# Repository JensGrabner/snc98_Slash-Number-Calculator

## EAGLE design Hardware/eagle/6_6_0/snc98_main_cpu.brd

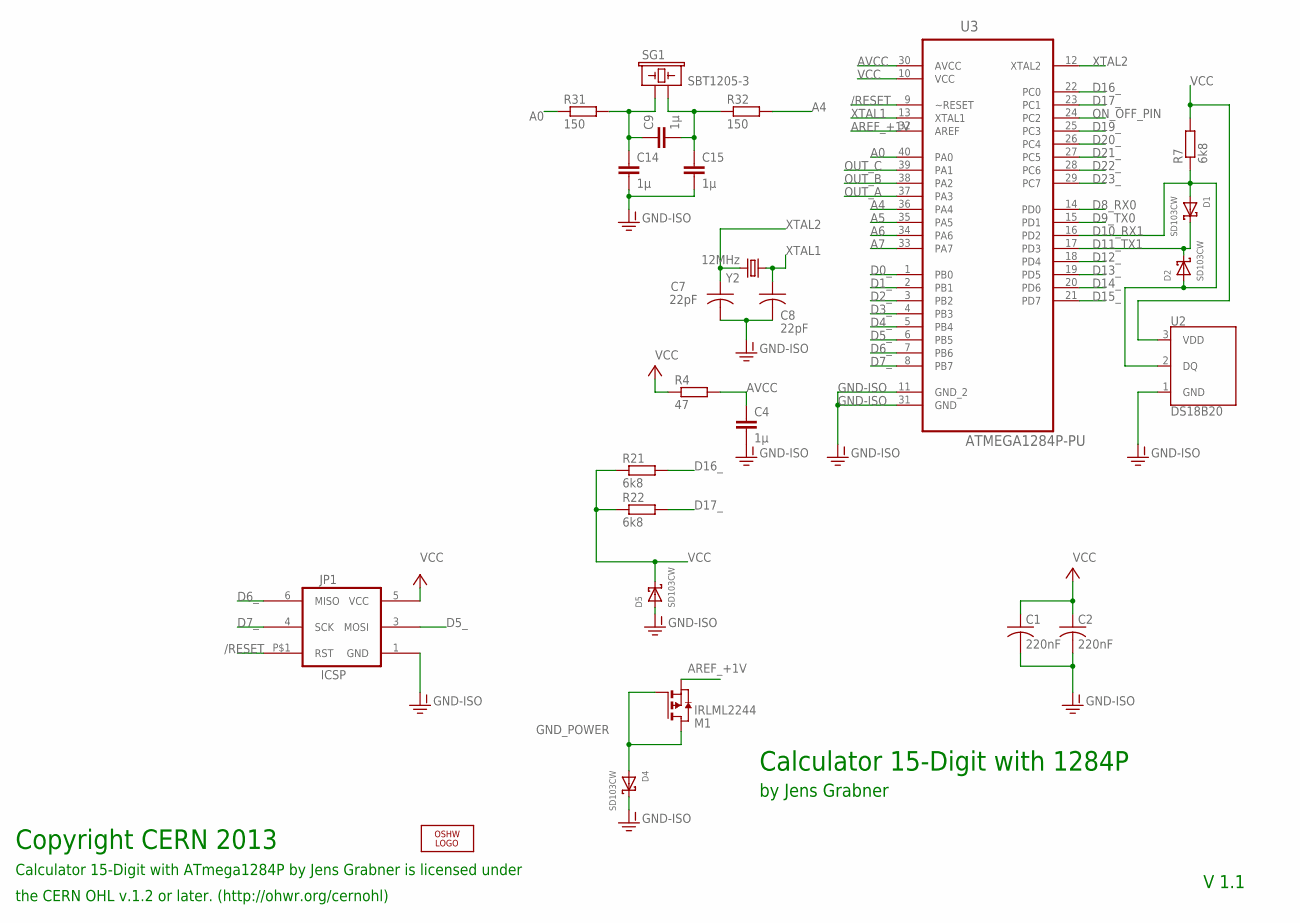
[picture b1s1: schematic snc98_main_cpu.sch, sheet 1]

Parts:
C1, C2: 220nF; C1206K
C4, C9, C14, C15: 1µ; C1206K
C7, C8: 22pF; C0805K
D1: SD103CW; SOD-323; MPN SD103CW-7-F
D2: SD103CW; SOD-123; MPN SD103CW-7-F
D4, D5: SD103CW; SOD-123F; MPN SD103CW-7-F
JP1: ICSP; 2X3_SMD_VERTICAL
LOGO1: OSHW_LOGO_8MILX0150-NT; OSHW_8X150_NOTEXT
M1: IRLML2244; SOT-23; MPN IRLML2244TRPBF
R4: 47; R1206
R7, R21, R22: 6k8; R1206
R31, R32: 150; R1206
SG1: SBT1205-3; BUZZER-12MM-NS
U2: DS18B20; TO-92-AMMO
U3: ATMEGA1284P-PU; DIP254P1524X483-40
Y2: 12MHz; HC49U-V

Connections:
/RESET: JP1.P$1 (RST), U3.9 (~RESET); also elsewhere on the board
A0: R31.1, U3.40 (PA0)
A4: R32.2, U3.36 (PA4)
A5: U3.35 (PA5); also elsewhere on the board
A6: U3.34 (PA6); also elsewhere on the board
A7: U3.33 (PA7); also elsewhere on the board
AREF_+1V: M1.2 (S), U3.32 (AREF); also elsewhere on the board
AVCC: C4.1, R4.2, U3.30 (AVCC)
D0_: U3.1 (PB0); also elsewhere on the board
D1_: U3.2 (PB1); also elsewhere on the board
D2_: U3.3 (PB2); also elsewhere on the board
D3_: U3.4 (PB3); also elsewhere on the board
D4_: U3.5 (PB4); also elsewhere on the board
D5_: JP1.3 (MOSI), U3.6 (PB5)
D6_: JP1.6 (MISO), U3.7 (PB6); also elsewhere on the board
D7_: JP1.4 (SCK), U3.8 (PB7); also elsewhere on the board
D8_RX0: U3.14 (PD0); also elsewhere on the board
D9_TX0: U3.15 (PD1); also elsewhere on the board
D10_RX1: D1.A, D2.A, R7.1, U2.2 (DQ), U3.16 (PD2)
D11_TX1: D1.C, D2.C, U3.17 (PD3)
D12_: U3.18 (PD4)
D13_: U3.19 (PD5); also elsewhere on the board
D14_: U3.20 (PD6); also elsewhere on the board
D15_: U3.21 (PD7); also elsewhere on the board
D16_: R21.2, U3.22 (PC0)
D17_: R22.2, U3.23 (PC1)
D19_: U3.25 (PC3); also elsewhere on the board
D20_: U3.26 (PC4); also elsewhere on the board
D21_: U3.27 (PC5); also elsewhere on the board
D22_: U3.28 (PC6); also elsewhere on the board
D23_: U3.29 (PC7); also elsewhere on the board
GND-ISO: C1.2, C2.2, C4.2, C7.2, C8.2, C14.2, C15.2, D4.C, D5.A, JP1.1 (GND), U2.1 (GND), U3.11 (GND_2), U3.31 (GND); also elsewhere on the board
GND_POWER: D4.A, M1.1 (G), M1.3 (D)
unnamed: C9.2, C15.1, R32.1, SG1.- (2)
unnamed: C9.1, C14.1, R31.2, SG1.+ (1)
ON_OFF_PIN: U3.24 (PC2); also elsewhere on the board
OUT_A: U3.37 (PA3); also elsewhere on the board
OUT_B: U3.38 (PA2); also elsewhere on the board
OUT_C: U3.39 (PA1); also elsewhere on the board
VCC: C1.1, C2.1, D5.C, JP1.5 (VCC), R4.1, R7.2, R21.1, R22.1, U2.3 (VDD), U3.10 (VCC); also elsewhere on the board
XTAL1: C8.1, U3.13 (XTAL1), Y2.1
XTAL2: C7.1, U3.12 (XTAL2), Y2.2

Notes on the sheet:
Calculator 15-Digit with 1284P
by Jens Grabner
V 1.1
Calculator 15-Digit with ATmega1284P by Jens Grabner is licensed under
Copyright CERN 2013
the CERN OHL v.1.2 or later. (http://ohwr.org/cernohl)

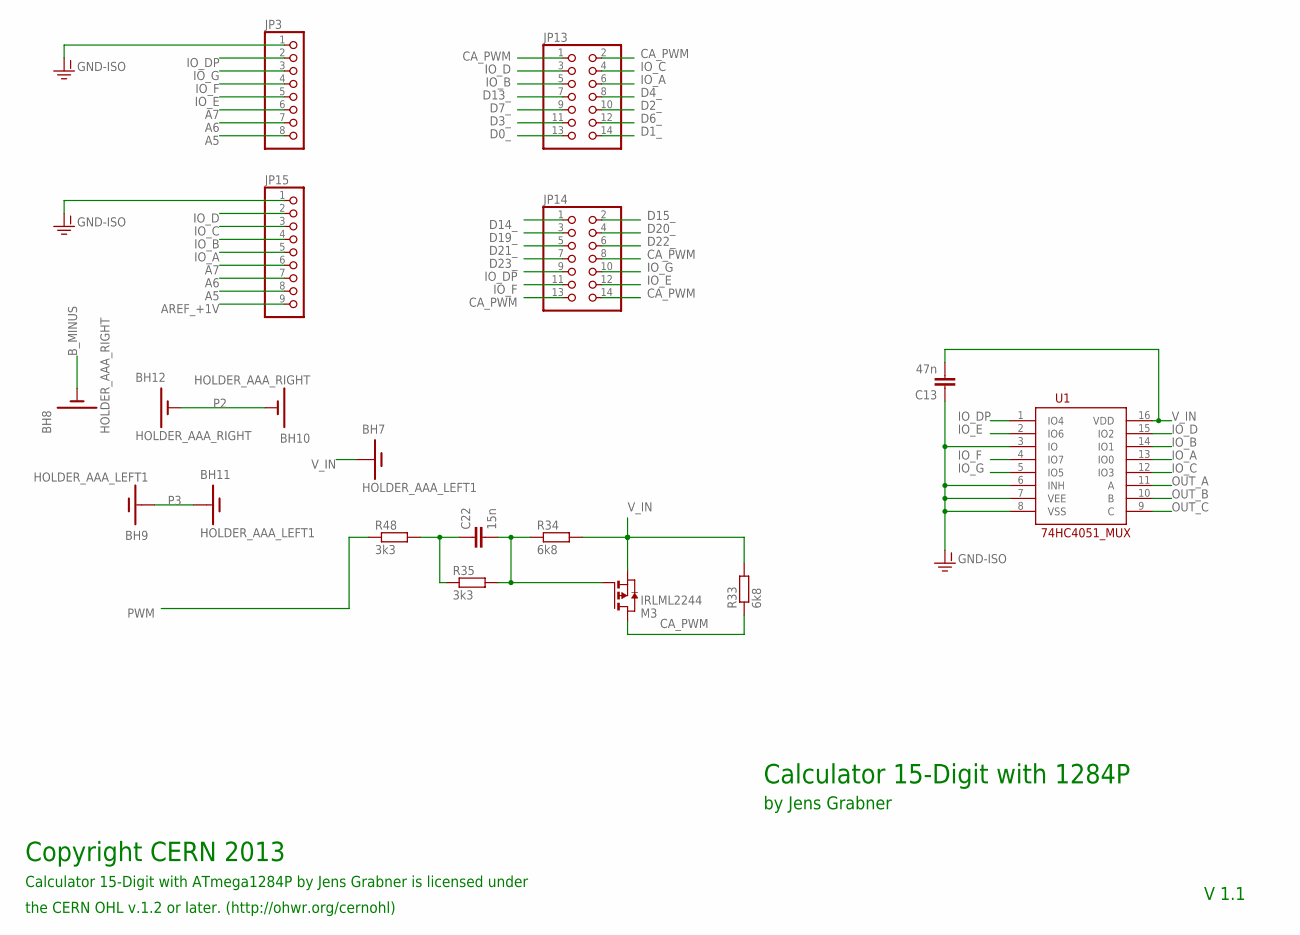
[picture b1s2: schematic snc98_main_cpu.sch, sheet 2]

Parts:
BH7, BH9, BH11: HOLDER_AAA_LEFT1; BATTERY-AAA-LEFT
BH8, BH10, BH12: HOLDER_AAA_RIGHT; BATTERY-AAA-RIGHT
C13: 47n; C1206K
C22: 15n; C1206K
JP3: PINHD-1X8CLEANBIG; 1X08-CLEANBIG
JP13, JP14: PINHD-2X7; 2X07
JP15: PINHD-1X9; 1X09-BIG
M3: IRLML2244; SOT-23; MPN IRLML2244TRPBF
R33, R34: 6k8; R1206
R35, R48: 3k3; R1206
U1: 74HC4051_MUX; SO16

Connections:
A5: JP3.8, JP15.8; also elsewhere on the board
A6: JP3.7, JP15.7; also elsewhere on the board
A7: JP3.6, JP15.6; also elsewhere on the board
A8: C22.1, R35.1, R48.2
AREF_+1V: JP15.9; also elsewhere on the board
B_MINUS: BH8.M1, BH8.M2, BH8.M3, BH8.M4; also elsewhere on the board
CA_PWM: JP13.1, JP13.2, JP14.8, JP14.13, JP14.14, M3.3 (D), R33.1
D0_: JP13.13; also elsewhere on the board
D1_: JP13.14; also elsewhere on the board
D2_: JP13.10; also elsewhere on the board
D3_: JP13.11; also elsewhere on the board
D4_: JP13.8; also elsewhere on the board
D6_: JP13.12; also elsewhere on the board
D7_: JP13.9; also elsewhere on the board
D13_: JP13.7; also elsewhere on the board
D14_: JP14.1; also elsewhere on the board
D15_: JP14.2; also elsewhere on the board
D19_: JP14.3; also elsewhere on the board
D20_: JP14.4; also elsewhere on the board
D21_: JP14.5; also elsewhere on the board
D22_: JP14.6; also elsewhere on the board
D23_: JP14.7; also elsewhere on the board
GND-ISO: C13.1, JP3.1, JP15.1, U1.3 (IO), U1.6 (INH), U1.7 (VEE), U1.8 (VSS); also elsewhere on the board
IO_A: JP13.6, JP15.5, U1.13 (IO0)
IO_B: JP13.5, JP15.4, U1.14 (IO1)
IO_C: JP13.4, JP15.3, U1.12 (IO3)
IO_D: JP13.3, JP15.2, U1.15 (IO2)
IO_DP: JP3.2, JP14.9, U1.1 (IO4)
IO_E: JP3.5, JP14.12, U1.2 (IO6)
IO_F: JP3.4, JP14.11, U1.4 (IO7)
IO_G: JP3.3, JP14.10, U1.5 (IO5)
unnamed: C22.2, M3.1 (G), R34.1, R35.2
OUT_A: U1.11 (A); also elsewhere on the board
OUT_B: U1.10 (B); also elsewhere on the board
OUT_C: U1.9 (C); also elsewhere on the board
P2: BH10.M1, BH10.M2, BH10.M3, BH10.M4, BH12.M1, BH12.M2, BH12.M3, BH12.M4
P3: BH9.P1, BH9.P2, BH9.P3, BH9.P4, BH11.P1, BH11.P2, BH11.P3, BH11.P4
PWM: R48.1
V_IN: BH7.P1, BH7.P2, BH7.P3, BH7.P4, C13.2, M3.2 (S), R33.2, R34.2, U1.16 (VDD); also elsewhere on the board

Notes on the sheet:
Calculator 15-Digit with 1284P
by Jens Grabner
V 1.1
Calculator 15-Digit with ATmega1284P by Jens Grabner is licensed under
Copyright CERN 2013
the CERN OHL v.1.2 or later. (http://ohwr.org/cernohl)

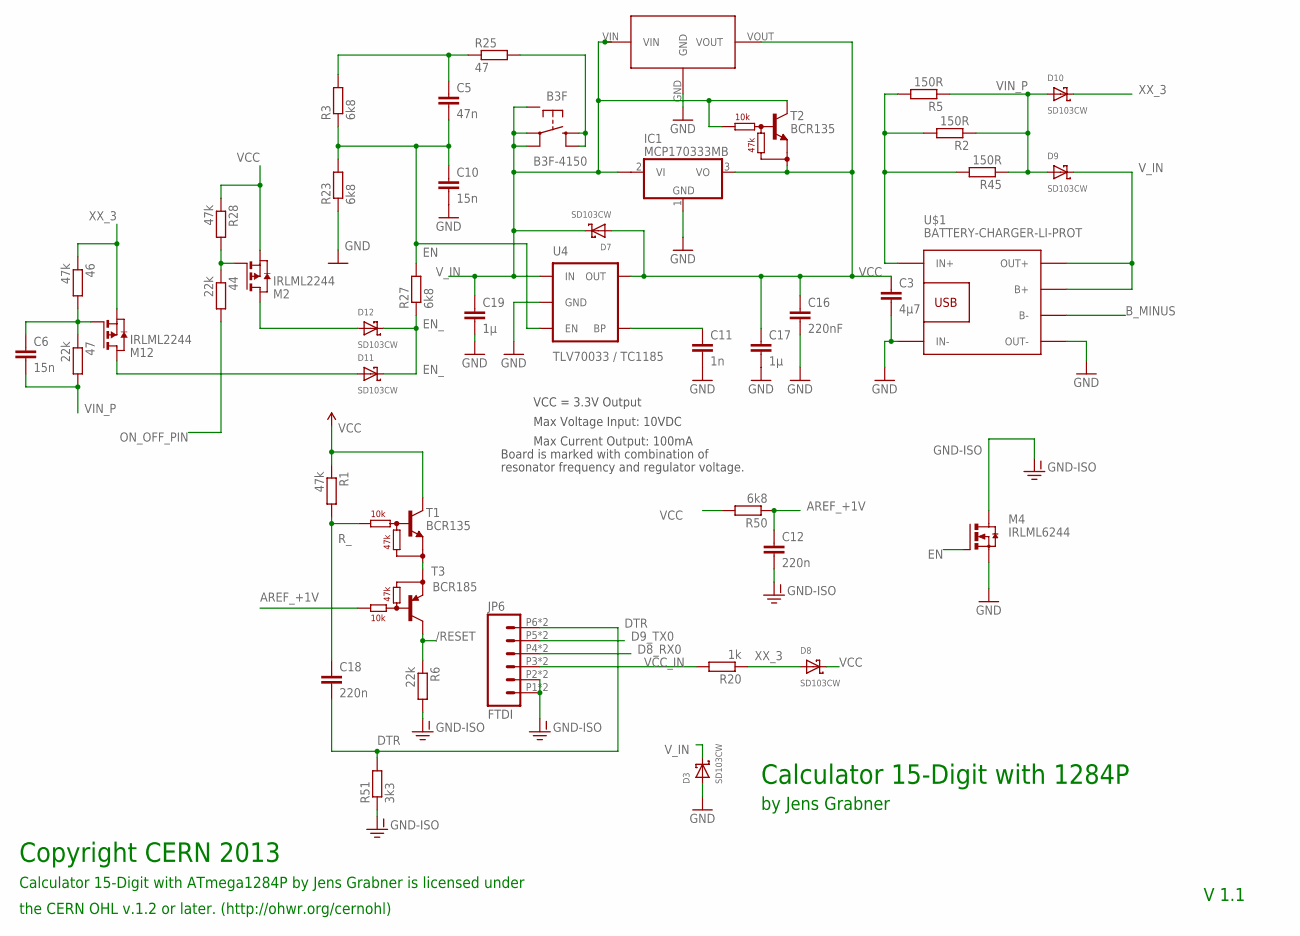
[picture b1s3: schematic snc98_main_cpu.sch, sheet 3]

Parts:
44, 47: 22k; R1206
46: 47k; R1206
C3: 4µ7; C1206K
C5: 47n; C1206K
C6, C10: 15n; C1206K
C11: 1n; 0805
C12: 220n; 0805
C16: 220nF; 0805
C17, C19: 1µ; C1206K
C18: 220n; C1206K
D3, D7, D8, D9, D10, D11, D12: SD103CW; SOD-123F; MPN SD103CW-7-F
IC1: MCP170333MB; SOT89
JP6: FTDI; 1X06_LOCK
M2, M12: IRLML2244; SOT-23; MPN IRLML2244TRPBF
M4: IRLML6244; SOT-23; MPN IRLML6244TRPBF
R1, R28: 47k; R1206
R2: 150R; 0204/5
R3, R23, R27, R50: 6k8; R1206
R5: 150R; 0207/10
R6: 22k; R1206
R20: 1k; R1206
R25: 47; R1206
R45: 150R; R1206
R51: 3k3; R1206
S3: B3F-4150; TACTILE-PTH-12MM; MPN B3F4150
T1, T2: BCR135; SOT23-BEC; MPN BCR135E6327HTSA1
T3: BCR185; SOT23-R_INFINEON; MPN DTA114YKAT146
U4: TLV70033 / TC1185; SOT23-5
U$1: BATTERY-CHARGER-LI-PROT
U$3: HT7333 / TS9011SCY; SOT89

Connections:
/RESET: R6.1, T3.C; also elsewhere on the board
A9: C5.1, R3.2, R25.1
AREF_+1V: C12.3 (1), R50.1, T3.B; also elsewhere on the board
B_MINUS: U$1.B-; also elsewhere on the board
CA_PWM1: D12.A, M2.3 (D)
CA_PWM2: D11.A, M12.3 (D)
D8_RX0: JP6.P4 (4), JP6.P4A (4); also elsewhere on the board
D9_TX0: JP6.P5 (5), JP6.P5A (5); also elsewhere on the board
DTR: C18.2, JP6.P6 (6), JP6.P6A (6), R51.2
EN: C5.2, C10.1, M4.1 (G), R3.1, R23.2, R27.2, U4.3 (EN)
EN_: D11.C, D12.C, R27.1
GND: C3.2, C10.2, C11.4 (2), C16.4 (2), C17.2, C19.2, D3.A, IC1.1 (GND), M4.2 (S), R23.1, U4.2 (GND), U$1.IN-, U$1.OUT-, U$3.GND
GND-ISO: C12.4 (2), JP6.P1 (1), JP6.P1A (1), JP6.P2 (2), JP6.P2A (2), M4.3 (D), R6.2, R51.1; also elsewhere on the board
unnamed: T1.E, T3.E
unnamed: C11.3 (1), U4.4 (BP)
unnamed: R25.2, S3.P$3 (3), S3.P$4 (4), S3.P$13 (3), S3.P$14 (4), S3.P$23 (3), S3.P$24 (4)
unnamed: 44.1, M2.1 (G), R28.2
unnamed: 46.2, 47.1, C6.1, M12.1 (G)
unnamed: R2.2, R5.2, R45.2, U$1.IN+
ON_OFF_PIN: 44.2; also elsewhere on the board
R_: C18.1, R1.2, T1.B
VCC: C3.1, C16.3 (1), C17.1, D7.A, D8.C, IC1.3 (VO), M2.2 (S), R1.1, R28.1, R50.2, T1.C, T2.E, U4.5 (OUT), U$3.VOUT; also elsewhere on the board
VCC_IN: JP6.P3 (3), JP6.P3A (3), R20.2
VIN_P: 47.2, C6.2, D9.A, D10.A, R2.1, R5.1, R45.1
V_IN: C19.1, D3.C, D7.C, D9.C, IC1.2@1 (VI1), S3.P$1 (1), S3.P$2 (2), S3.P$11 (1), S3.P$12 (2), S3.P$15 (5), S3.P$21 (1), S3.P$22 (2), T2.B, T2.C, U4.1 (IN), U$1.B+, U$1.OUT+, U$3.VIN; also elsewhere on the board
XX_3: 46.1, D8.A, D10.C, M12.2 (S), R20.1

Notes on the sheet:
Calculator 15-Digit with 1284P
by Jens Grabner
V 1.1
Calculator 15-Digit with ATmega1284P by Jens Grabner is licensed under
Copyright CERN 2013
the CERN OHL v.1.2 or later. (http://ohwr.org/cernohl)
Max Voltage Input: 10VDC
Max Current Output: 100mA
Board is marked with combination of
resonator frequency and regulator voltage.
VCC = 3.3V Output

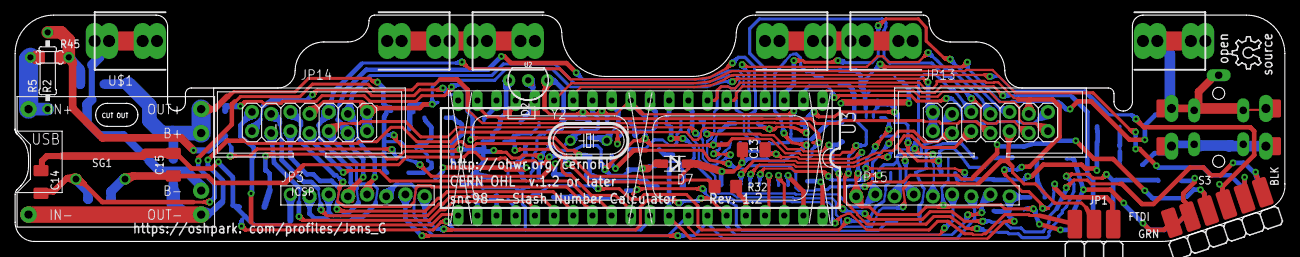
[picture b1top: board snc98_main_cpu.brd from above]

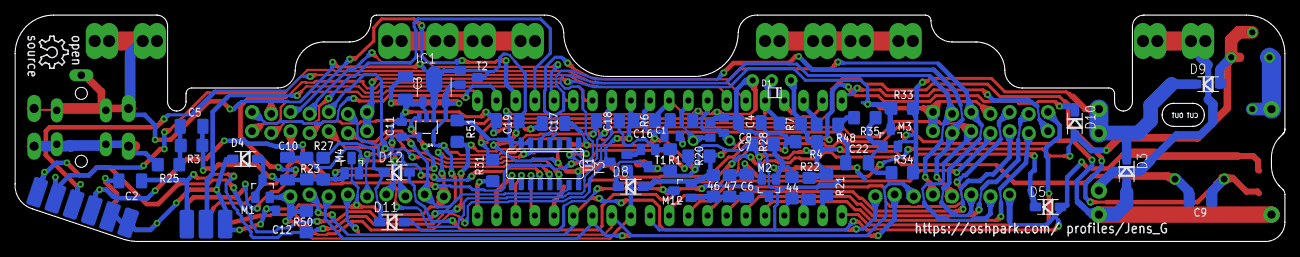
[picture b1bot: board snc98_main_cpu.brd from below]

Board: 2 copper layers, 168.2 x 30.0 mm, 89 parts (61 on the bottom side), 73 nets.

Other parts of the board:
LOGO2: OSHW_LOGO_8MILX0150-NT; OSHW_8X150_NOTEXT

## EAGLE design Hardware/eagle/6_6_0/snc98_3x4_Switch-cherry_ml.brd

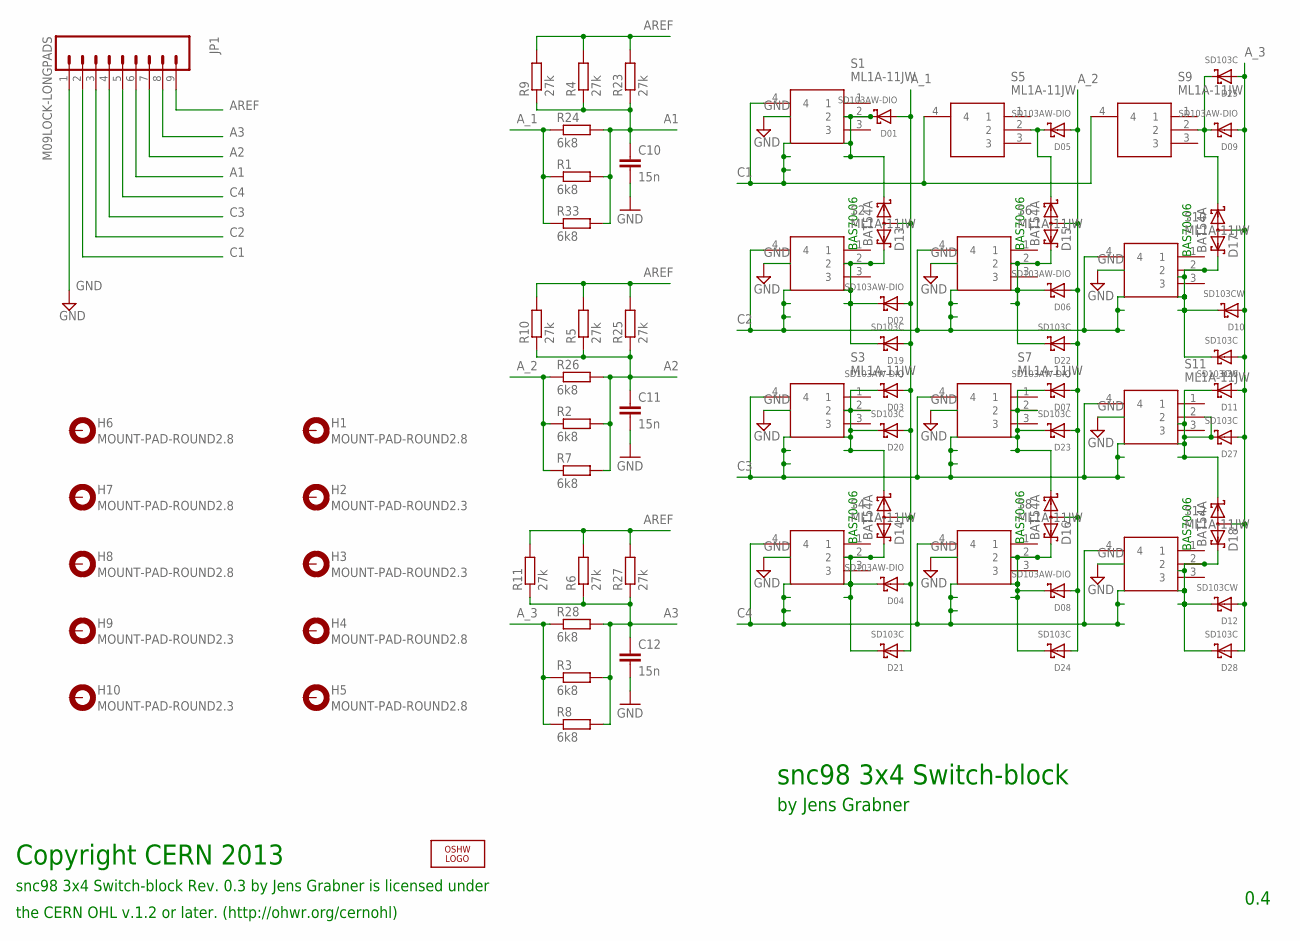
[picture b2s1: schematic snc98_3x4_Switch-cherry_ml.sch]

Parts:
C10, C11, C12: 15n; C1206K
D01, D02, D03, D04, D05, D06, D07, D08, D09: SD103AW-DIO; SOD-123F; MPN SD103CW-7-F
D10, D11, D12: SD103CW; SOD-123F; MPN SD103CW-7-F
D13, D14, D15, D16, D17, D18: BAT54A; SOT23
D19, D20, D21, D22, D23, D24, D25, D26, D27, D28: SD103C; 280MIL-TH; MPN SD103CW-7-F
H1, H4, H5, H6, H7, H8: MOUNT-PAD-ROUND2.8; 2,8-PAD
H2, H3, H9, H10: MOUNT-PAD-ROUND2.3; 2,3-PAD
JP1: M09LOCK-LONGPADS; 1X09_LOCK_LONGPADS
LOGO1: OSHW_LOGO_8MILX0150-NT; OSHW_8X150_NOTEXT
R1, R2, R3: 6k8; R1206
R4, R5, R6: 27k; R1206
R7, R8, R33: 6k8; M0805
R9, R10, R11: 27k; M0805
R23, R25, R27: 27k; 0204/5
R24, R26, R28: 6k8; 0204/5
S1, S2, S3, S4, S5, S6, S7, S8, S9, S10, S11, S12: ML1A-11JW; ML1A11JW

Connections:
A1: C10.1, JP1.6, R1.2, R4.1, R9.1, R23.1, R24.2, R33.2
A2: C11.1, JP1.7, R2.2, R5.1, R7.2, R10.1, R25.1, R26.2
A3: C12.1, JP1.8, R3.2, R6.1, R8.2, R11.1, R27.1, R28.2
AREF: JP1.9, R4.2, R5.2, R6.2, R9.2, R10.2, R11.2, R23.2, R25.2, R27.2
A_1: D01.A, D02.A, D03.A, D04.A, D13.3 (AA), D14.3 (AA), D19.P$1 (A), D20.P$1 (A), D21.P$1 (A), R1.1, R24.1, R33.1
A_2: D05.A, D06.A, D07.A, D08.A, D15.3 (AA), D16.3 (AA), D22.P$1 (A), D23.P$1 (A), D24.P$1 (A), R2.1, R7.1, R26.1
A_3: D09.A, D10.A, D11.A, D12.A, D17.3 (AA), D18.3 (AA), D25.P$1 (A), D26.P$1 (A), D27.P$1 (A), D28.P$1 (A), R3.1, R8.1, R28.1
C1: JP1.2, S1.4, S5.4, S9.4
C2: JP1.3, S2.4, S6.4, S10.4
C3: JP1.4, S3.4, S7.4, S11.4
C4: JP1.5, S4.4, S8.4, S12.4
GND: C10.2, C11.2, C12.2, JP1.1
unnamed: D04.C, D14.2 (K2), D21.P$2 (C), S4.2
unnamed: D01.C, D13.1 (K1), S1.2
unnamed: D05.C, D15.1 (K1), S5.2
unnamed: D09.C, D17.1 (K1), D25.P$2 (C), S9.2
unnamed: D10.C, D17.2 (K2), D26.P$2 (C), S10.2
unnamed: D02.C, D13.2 (K2), D19.P$2 (C), S2.2
unnamed: D11.C, D18.1 (K1), D27.P$2 (C), S11.2
unnamed: D12.C, D18.2 (K2), D28.P$2 (C), S12.2
unnamed: D06.C, D15.2 (K2), D22.P$2 (C), S6.2
unnamed: D07.C, D16.1 (K1), D23.P$2 (C), S7.2
unnamed: D08.C, D16.2 (K2), D24.P$2 (C), S8.2
unnamed: D03.C, D14.1 (K1), D20.P$2 (C), S3.2

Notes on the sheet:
snc98 3x4 Switch-block
by Jens Grabner
0.4
snc98 3x4 Switch-block Rev. 0.3 by Jens Grabner is licensed under
Copyright CERN 2013
the CERN OHL v.1.2 or later. (http://ohwr.org/cernohl)
BAS70-06

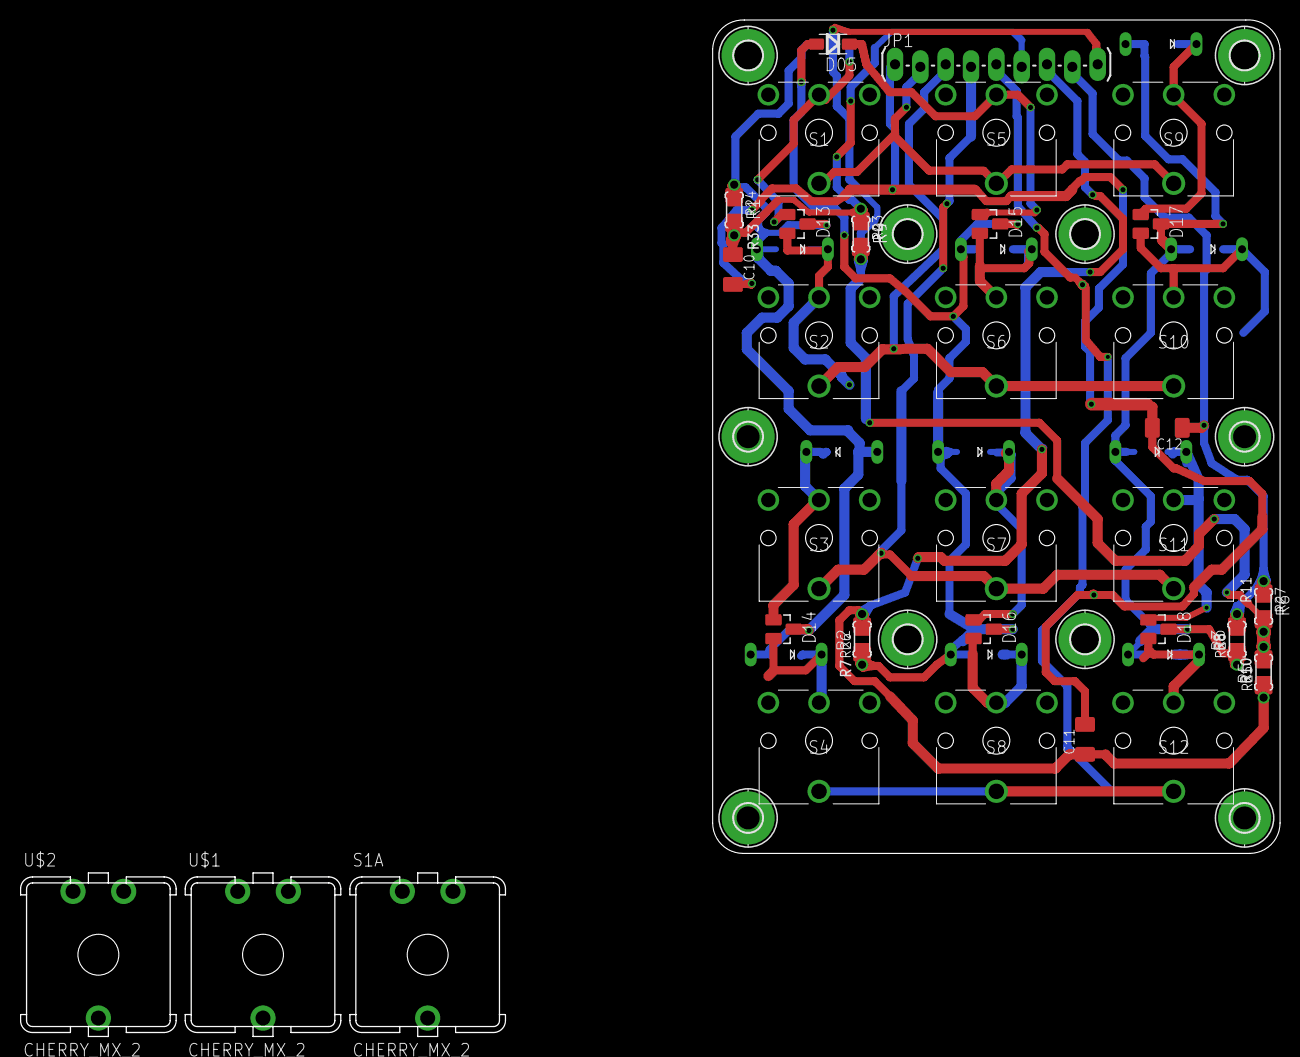
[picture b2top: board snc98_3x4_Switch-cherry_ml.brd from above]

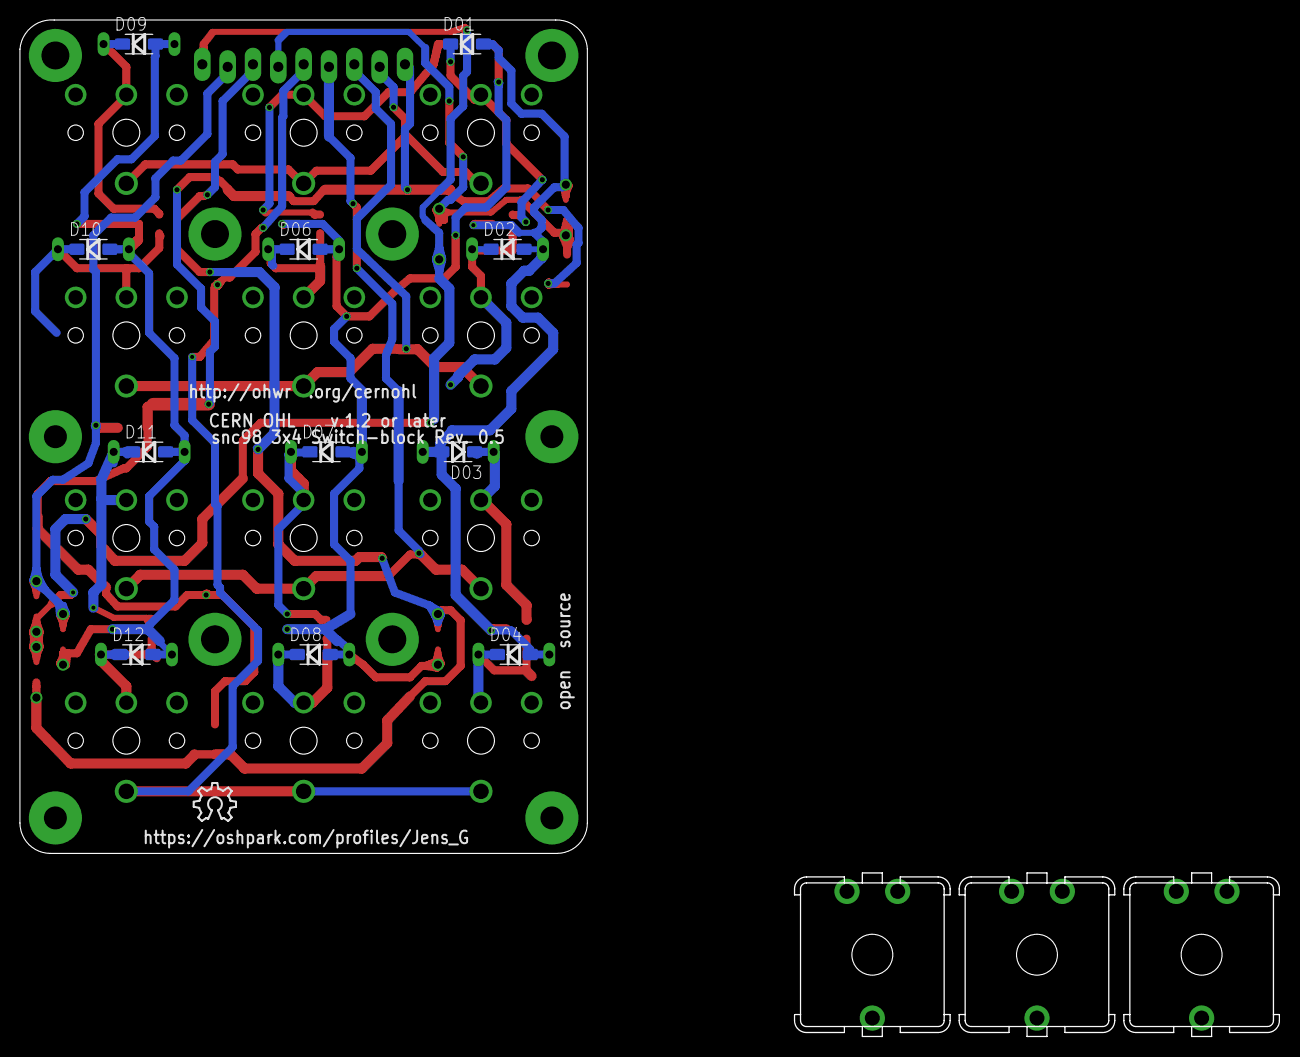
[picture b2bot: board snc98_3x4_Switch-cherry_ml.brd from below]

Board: 2 copper layers, 56.9 x 83.6 mm, 76 parts (12 on the bottom side), 24 nets.

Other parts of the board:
S1A: CHERRY_MX_2; CHERRY_MX
U$1, U$2: CHERRY_MX_2; CHERRY_MX

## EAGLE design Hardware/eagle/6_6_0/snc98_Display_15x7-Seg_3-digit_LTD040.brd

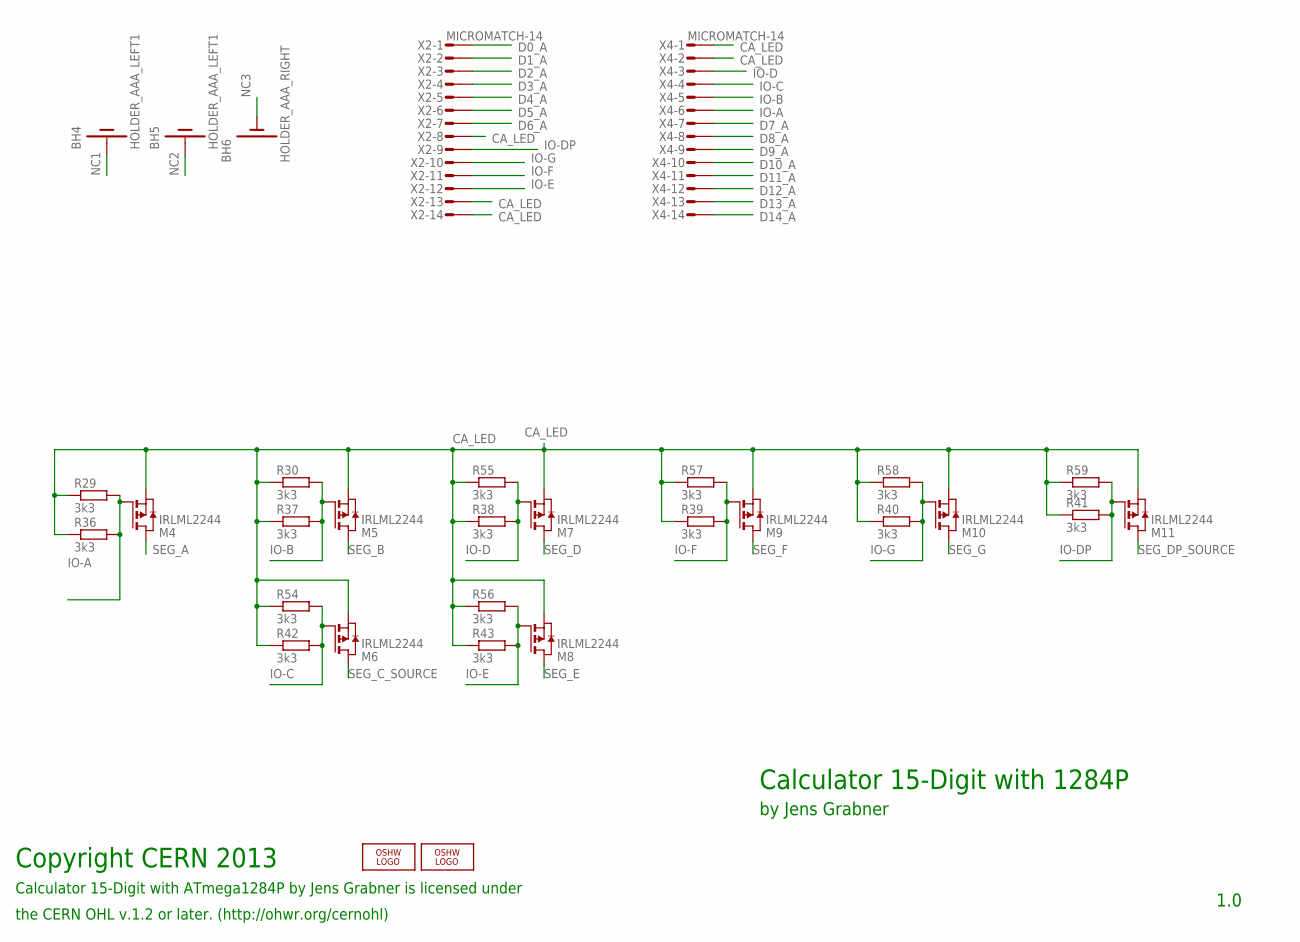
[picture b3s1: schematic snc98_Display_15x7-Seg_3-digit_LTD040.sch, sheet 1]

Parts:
BH4, BH5: HOLDER_AAA_LEFT1; BATTERY-AAA-LEFT
BH6: HOLDER_AAA_RIGHT; BATTERY-AAA-RIGHT
LOGO1: OSHW_LOGO_8MILX0150-NT; OSHW_8X150_NOTEXT
LOGO3: OSHW_LOGO_6MILX0100-NT; OSHW_6X100_NOTEXT
M4, M5, M6, M7, M8, M9, M10, M11: IRLML2244; SOT-23
R29, R30, R54, R55, R56, R57, R58, R59: 3k3; 0204/5
R36, R37, R38, R39, R40, R41, R42, R43: 3k3; R1206
X2, X4: MICROMATCH-14

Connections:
CA_LED: M4.2 (S), M5.2 (S), M6.2 (S), M7.2 (S), M8.2 (S), M9.2 (S), M10.2 (S), M11.2 (S), R29.1, R30.1, R36.1, R37.1, R38.1, R39.1, R40.1, R41.1, R42.1, R43.1, R54.1, R55.1, R56.1, R57.1, R58.1, R59.1, X2.8, X2.13, X2.14, X4.1, X4.2; also elsewhere on the board
D0_A: X2.1; also elsewhere on the board
D1_A: X2.2; also elsewhere on the board
D2_A: X2.3; also elsewhere on the board
D3_A: X2.4; also elsewhere on the board
D4_A: X2.5; also elsewhere on the board
D5_A: X2.6; also elsewhere on the board
D6_A: X2.7; also elsewhere on the board
D7_A: X4.7; also elsewhere on the board
D8_A: X4.8; also elsewhere on the board
D9_A: X4.9; also elsewhere on the board
D10_A: X4.10; also elsewhere on the board
D11_A: X4.11; also elsewhere on the board
D12_A: X4.12; also elsewhere on the board
D13_A: X4.13; also elsewhere on the board
D14_A: X4.14; also elsewhere on the board
IO-A: M4.1 (G), R29.2, R36.2, X4.6; also elsewhere on the board
IO-B: M5.1 (G), R30.2, R37.2, X4.5; also elsewhere on the board
IO-C: M6.1 (G), R42.2, R54.2, X4.4; also elsewhere on the board
IO-D: M7.1 (G), R38.2, R55.2, X4.3; also elsewhere on the board
IO-DP: M11.1 (G), R41.2, R59.2, X2.9; also elsewhere on the board
IO-E: M8.1 (G), R43.2, R56.2, X2.12; also elsewhere on the board
IO-F: M9.1 (G), R39.2, R57.2, X2.11; also elsewhere on the board
IO-G: M10.1 (G), R40.2, R58.2, X2.10; also elsewhere on the board
NC1: BH4.P1, BH4.P2, BH4.P3, BH4.P4
NC2: BH5.P1, BH5.P2, BH5.P3, BH5.P4
NC3: BH6.M1, BH6.M2, BH6.M3, BH6.M4
SEG_A: M4.3 (D); also elsewhere on the board
SEG_B: M5.3 (D); also elsewhere on the board
SEG_C_SOURCE: M6.3 (D); also elsewhere on the board
SEG_D: M7.3 (D); also elsewhere on the board
SEG_DP_SOURCE: M11.3 (D); also elsewhere on the board
SEG_E: M8.3 (D); also elsewhere on the board
SEG_F: M9.3 (D); also elsewhere on the board
SEG_G: M10.3 (D); also elsewhere on the board

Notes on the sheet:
Calculator 15-Digit with 1284P
by Jens Grabner
1.0
Calculator 15-Digit with ATmega1284P by Jens Grabner is licensed under
Copyright CERN 2013
the CERN OHL v.1.2 or later. (http://ohwr.org/cernohl)

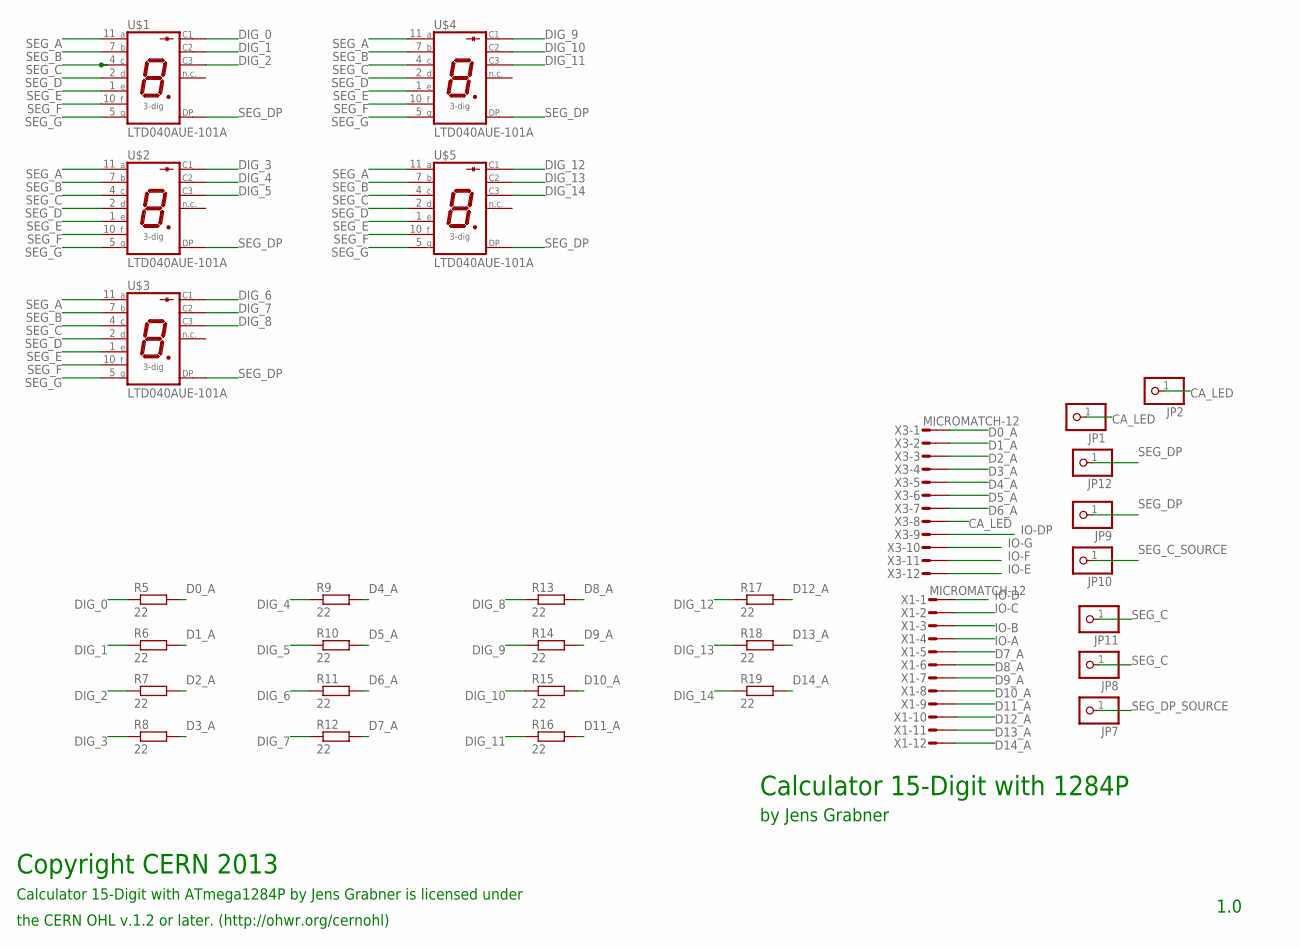
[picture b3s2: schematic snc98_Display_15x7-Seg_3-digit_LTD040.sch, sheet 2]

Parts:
JP1, JP2, JP7, JP8, JP9, JP10, JP11, JP12: PINHD-1X1; 1X01
R5, R6, R7, R8, R9, R10, R11, R12, R13, R14, R15, R16, R17, R18, R19: 22; R1210
U$1, U$2, U$3, U$4, U$5: LTD040AUE-101A
X1, X3: MICROMATCH-12

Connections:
CA_LED: JP1.1, JP2.1, X3.8; also elsewhere on the board
D0_A: R5.2, X3.1; also elsewhere on the board
D1_A: R6.2, X3.2; also elsewhere on the board
D2_A: R7.2, X3.3; also elsewhere on the board
D3_A: R8.2, X3.4; also elsewhere on the board
D4_A: R9.2, X3.5; also elsewhere on the board
D5_A: R10.2, X3.6; also elsewhere on the board
D6_A: R11.2, X3.7; also elsewhere on the board
D7_A: R12.2, X1.5; also elsewhere on the board
D8_A: R13.2, X1.6; also elsewhere on the board
D9_A: R14.2, X1.7; also elsewhere on the board
D10_A: R15.2, X1.8; also elsewhere on the board
D11_A: R16.2, X1.9; also elsewhere on the board
D12_A: R17.2, X1.10; also elsewhere on the board
D13_A: R18.2, X1.11; also elsewhere on the board
D14_A: R19.2, X1.12; also elsewhere on the board
DIG_0: R5.1, U$1.12 (C1)
DIG_1: R6.1, U$1.9 (C2)
DIG_2: R7.1, U$1.8 (C3)
DIG_3: R8.1, U$2.12 (C1)
DIG_4: R9.1, U$2.9 (C2)
DIG_5: R10.1, U$2.8 (C3)
DIG_6: R11.1, U$3.12 (C1)
DIG_7: R12.1, U$3.9 (C2)
DIG_8: R13.1, U$3.8 (C3)
DIG_9: R14.1, U$4.12 (C1)
DIG_10: R15.1, U$4.9 (C2)
DIG_11: R16.1, U$4.8 (C3)
DIG_12: R17.1, U$5.12 (C1)
DIG_13: R18.1, U$5.9 (C2)
DIG_14: R19.1, U$5.8 (C3)
IO-A: X1.4; also elsewhere on the board
IO-B: X1.3; also elsewhere on the board
IO-C: X1.2; also elsewhere on the board
IO-D: X1.1; also elsewhere on the board
IO-DP: X3.9; also elsewhere on the board
IO-E: X3.12; also elsewhere on the board
IO-F: X3.11; also elsewhere on the board
IO-G: X3.10; also elsewhere on the board
SEG_A: U$1.11 (A), U$2.11 (A), U$3.11 (A), U$4.11 (A), U$5.11 (A); also elsewhere on the board
SEG_B: U$1.7 (B), U$2.7 (B), U$3.7 (B), U$4.7 (B), U$5.7 (B); also elsewhere on the board
SEG_C: JP8.1, JP11.1, U$1.4 (C), U$2.4 (C), U$3.4 (C), U$4.4 (C), U$5.4 (C)
SEG_C_SOURCE: JP10.1; also elsewhere on the board
SEG_D: U$1.2 (D), U$2.2 (D), U$3.2 (D), U$4.2 (D), U$5.2 (D); also elsewhere on the board
SEG_DP: JP9.1, JP12.1, U$1.3 (DP), U$2.3 (DP), U$3.3 (DP), U$4.3 (DP), U$5.3 (DP)
SEG_DP_SOURCE: JP7.1; also elsewhere on the board
SEG_E: U$1.1 (E), U$2.1 (E), U$3.1 (E), U$4.1 (E), U$5.1 (E); also elsewhere on the board
SEG_F: U$1.10 (F), U$2.10 (F), U$3.10 (F), U$4.10 (F), U$5.10 (F); also elsewhere on the board
SEG_G: U$1.5 (G), U$2.5 (G), U$3.5 (G), U$4.5 (G), U$5.5 (G); also elsewhere on the board

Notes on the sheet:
Calculator 15-Digit with 1284P
by Jens Grabner
1.0
Calculator 15-Digit with ATmega1284P by Jens Grabner is licensed under
Copyright CERN 2013
the CERN OHL v.1.2 or later. (http://ohwr.org/cernohl)

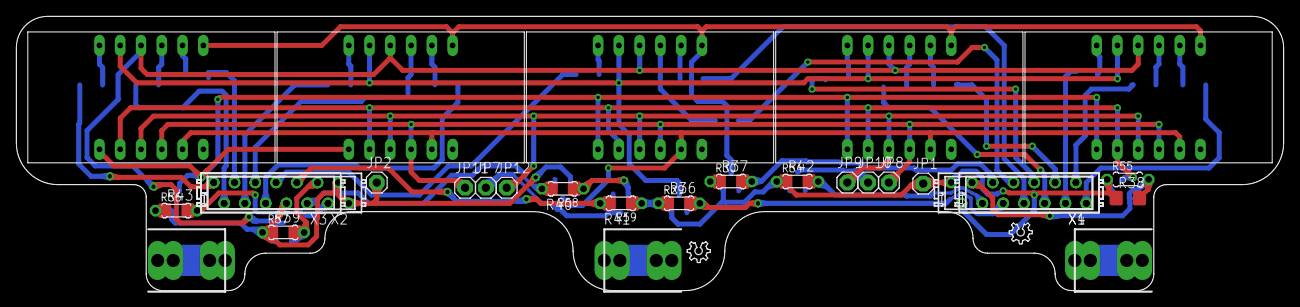
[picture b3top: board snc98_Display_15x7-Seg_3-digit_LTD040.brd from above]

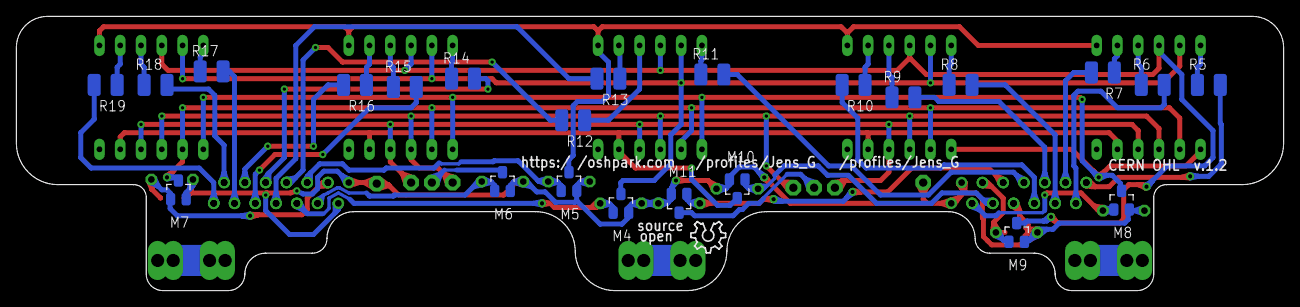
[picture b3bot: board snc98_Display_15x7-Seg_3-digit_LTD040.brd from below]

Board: 2 copper layers, 154.9 x 33.5 mm, 62 parts (24 on the bottom side), 52 nets.

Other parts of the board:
LOGO2: OSHW_LOGO_6MILX0100-NT; OSHW_6X100_NOTEXT

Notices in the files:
Hardware/eagle/snc98_Display_15x7-Seg_3-digit_LTD056.brd:
CERN OHL  v.1.3
parts and their libraries:
SparkFun-Connectors: Licensing: CC v3.0 Share-Alike You are welcome to use this library for commercial purposes.
SparkFun-Electromechanical: Licensing: Creative Commons ShareAlike 4.0 International - https://creativecommons.org/licenses/by-sa/4.0
